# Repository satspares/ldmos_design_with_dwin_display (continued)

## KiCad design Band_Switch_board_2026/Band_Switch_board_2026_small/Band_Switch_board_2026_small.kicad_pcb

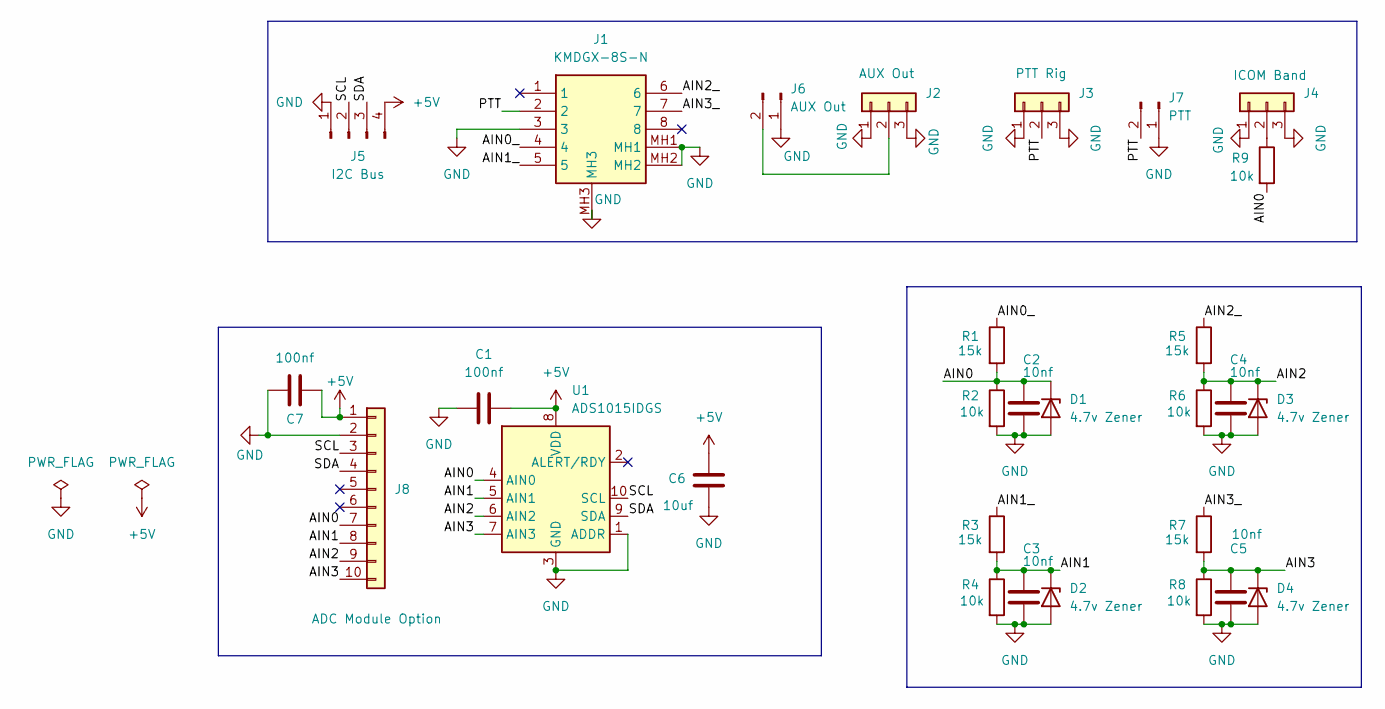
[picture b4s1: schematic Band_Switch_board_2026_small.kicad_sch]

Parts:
C1, C7: 100nf; C_Disc_D6.0mm_W2.5mm_P5.00mm
C2, C3, C4, C5: 10nf; C_Disc_D3.4mm_W2.1mm_P2.50mm
C6: 10uf; CP_Radial_Tantal_D5.0mm_P2.50mm
D1, D2, D3, D4: 4.7v Zener; D_DO-35_SOD27_P7.62mm_Horizontal
J1: KMDGX-8S-N; KMDGX8SN; Mouser Part Number 806-KMDGX-8S-N
J2: AUX Out; BarrelJack__Horizontal_Band_Switch
J3: PTT Rig; BarrelJack__Horizontal_Band_Switch
J4: ICOM Band; BarrelJack__Horizontal_Band_Switch
J5: I2C Bus; JST_EH_B4B-EH-A_1x04_P2.50mm_Vertical
J6: AUX Out; JST_EH_B2B-EH-A_1x02_P2.50mm_Vertical
J7: PTT; JST_EH_B2B-EH-A_1x02_P2.50mm_Vertical
J8: ADC Module Option; PinHeader_1x10_P2.54mm_Vertical_ADC
R1, R3, R5, R7: 15k; R_Axial_DIN0207_L6.3mm_D2.5mm_P7.62mm_Horizontal
R2, R4, R6, R8, R9: 10k; R_Axial_DIN0207_L6.3mm_D2.5mm_P7.62mm_Horizontal
U1: ADS1015IDGS; TSSOP-10_3x3mm_P0.5mm

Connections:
+5V: C1.2, C6.1, C7.2, J5.4, J8.1, U1.8 (VDD)
/AIN0: C2.1, D1.1 (K), J8.7, R1.2, R2.1, R9.2, U1.4 (AIN0)
/AIN0_: J1.4, R1.1
/AIN1: C3.1, D2.1 (K), J8.8, R3.2, R4.1, U1.5 (AIN1)
/AIN1_: J1.5, R3.1
/AIN2: C4.1, D3.1 (K), J8.9, R5.2, R6.1, U1.6 (AIN2)
/AIN2_: J1.6, R5.1
/AIN3: C5.1, D4.1 (K), J8.10, R7.2, R8.1, U1.7 (AIN3)
/AIN3_: J1.7, R7.1
/PTT: J1.2, J3.2, J7.2
/SCL: J5.2, J8.3, U1.10 (SCL)
/SDA: J5.3, J8.4, U1.9 (SDA)
GND: C1.1, C2.2, C3.2, C4.2, C5.2, C6.2, C7.1, D1.2 (A), D2.2 (A), D3.2 (A), D4.2 (A), J1.3, J1.MH1, J1.MH2, J1.MH3, J2.1, J2.3, J3.1, J3.3, J4.1, J4.3, J5.1, J6.1, J7.1, J8.2, R2.2, R4.2, R6.2, R8.2, U1.1 (ADDR), U1.3 (GND)
unnamed: J2.2, J6.2
unnamed: J4.2, R9.1

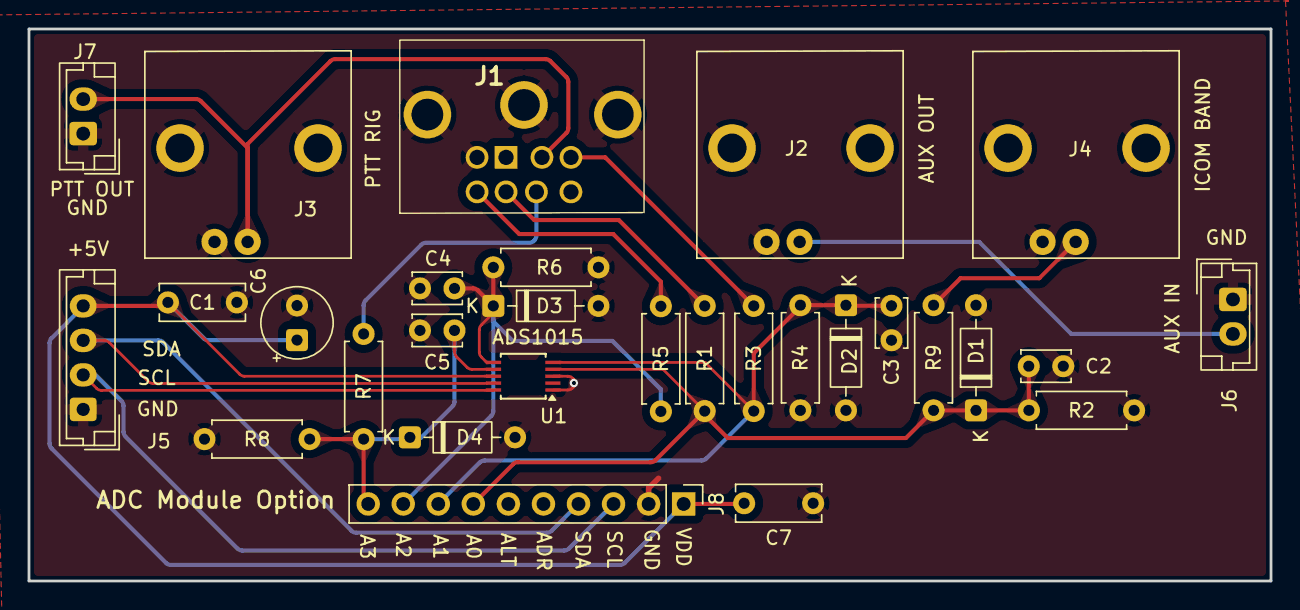
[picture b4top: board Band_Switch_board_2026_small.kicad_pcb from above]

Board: 2 copper layers, 90.0 x 40.0 mm, 29 parts (0 on the bottom side), 15 nets.

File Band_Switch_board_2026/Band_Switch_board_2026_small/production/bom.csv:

Designator,Footprint,Quantity,Value,LCSC Part #
"C1, C7",C_Disc_D6.0mm_W2.5mm_P5.00mm,2,100nf,
"C2, C3, C4, C5",C_Disc_D3.4mm_W2.1mm_P2.50mm,4,10nf,
C6,CP_Radial_Tantal_D5.0mm_P2.50mm,1,10uf,
"D1, D2, D3, D4",D_DO-35_SOD27_P7.62mm_Horizontal,4,4.7v Zener,
J1,KMDGX8SN,1,KMDGX-8S-N,
J2,BarrelJack__Horizontal_Band_Switch,1,AUX Out,
J3,BarrelJack__Horizontal_Band_Switch,1,PTT Rig,
J4,BarrelJack__Horizontal_Band_Switch,1,ICOM Band,
J5,JST_EH_B4B-EH-A_1x04_P2.50mm_Vertical,1,I2C Bus,
J6,JST_EH_B2B-EH-A_1x02_P2.50mm_Vertical,1,AUX Out,
J7,JST_EH_B2B-EH-A_1x02_P2.50mm_Vertical,1,PTT,
J8,PinHeader_1x10_P2.54mm_Vertical_ADC,1,ADC Module,
"R1, R3, R5, R7",R_Axial_DIN0207_L6.3mm_D2.5mm_P7.62mm_Horizontal,4,15k,
"R2, R4, R6, R8, R9",R_Axial_DIN0207_L6.3mm_D2.5mm_P7.62mm_Horizontal,5,10k,
U1,TSSOP-10_3x3mm_P0.5mm,1,ADS1015IDGS,

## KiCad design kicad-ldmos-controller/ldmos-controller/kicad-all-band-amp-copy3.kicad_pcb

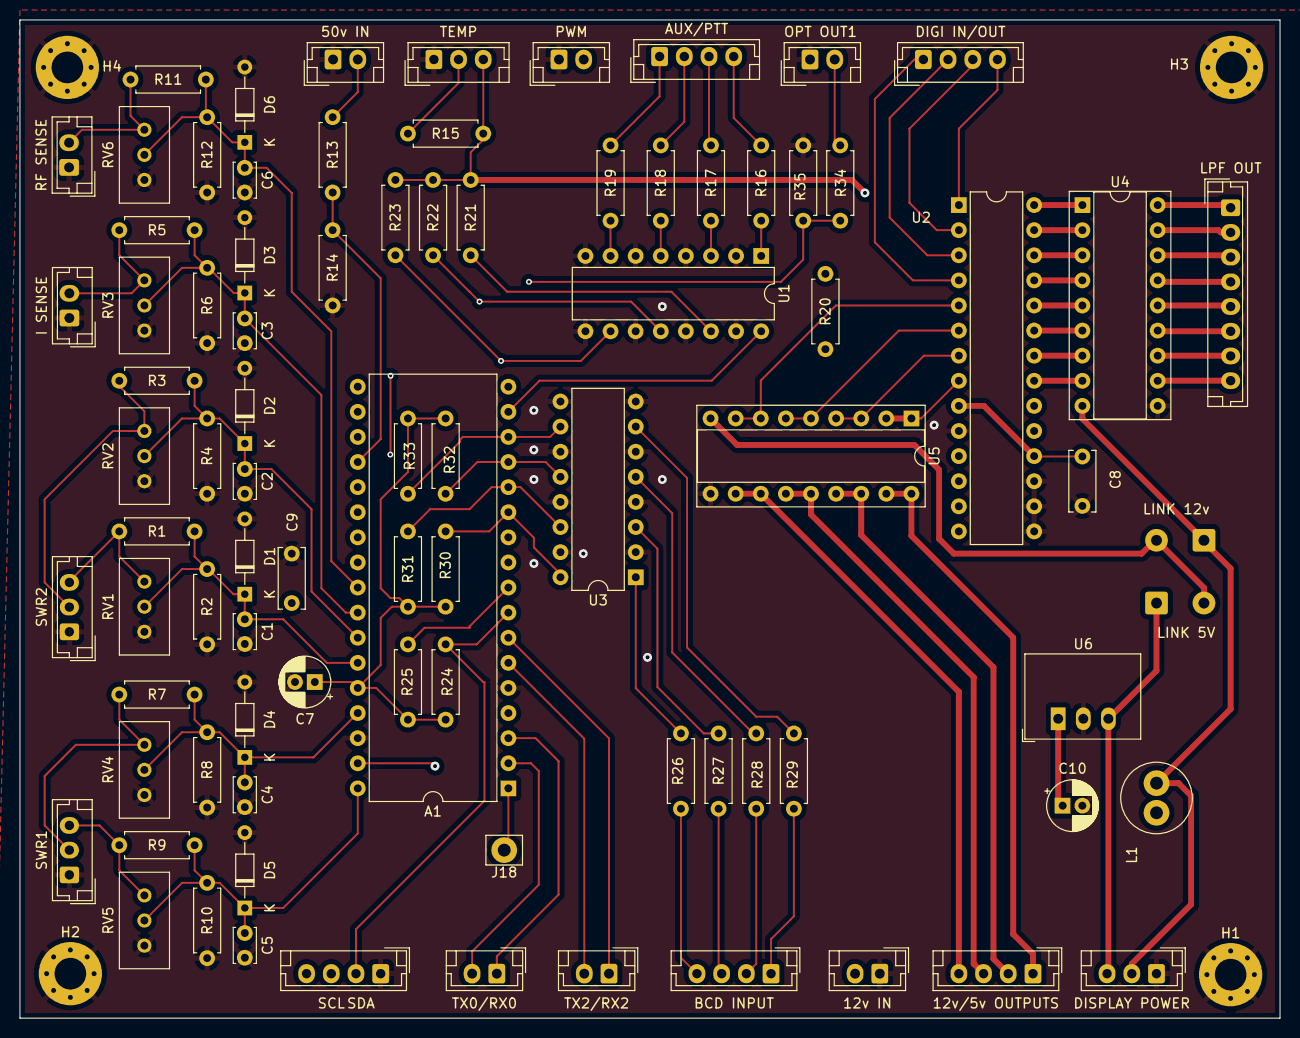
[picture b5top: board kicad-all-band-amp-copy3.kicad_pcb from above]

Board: 4 copper layers, 127.5 x 101.0 mm, 90 parts (0 on the bottom side), 84 nets.

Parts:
12v IN: 12v Input; JST_EH_B2B-EH-A_1x02_P2.50mm_Vertical
12v/5v OUTPUTS: 12v/5v Outputs; JST_EH_B4B-EH-A_1x04_P2.50mm_Vertical
50v IN: 50v In.; JST_EH_B2B-EH-A_1x02_P2.50mm_Vertical
A1: Arduino_Nano_Every-4808; DIP-34_W15.24mm
AUX/PTT: Ext. In; JST_EH_B4B-EH-A_1x04_P2.50mm_Vertical
BCD INPUT: BCD Input; JST_EH_B4B-EH-A_1x04_P2.50mm_Vertical
C1, C2, C3, C4, C5, C6: 1nf; C_Disc_D3.4mm_W2.1mm_P2.50mm
C7: 10uf; CP_Radial_D5.0mm_P2.00mm
C8, C9: 100nf; C_Disc_D6.0mm_W2.5mm_P5.00mm
C10: 2.2uf; CP_Radial_D5.0mm_P2.00mm
D1, D2, D3, D4, D5, D6: D_Zener; D_DO-34_SOD68_P7.62mm_Horizontal
DIGI IN/OUT: Digi In/Out; JST_EH_B4B-EH-A_1x04_P2.50mm_Vertical
DISPLAY POWER: DISPLAY POWER; JST_EH_B3B-EH-A_1x03_P2.50mm_Vertical
H1, H2, H3, H4: MountingHole_Pad; MountingHole_3.2mm_M3_Pad_Via
I SENSE: I detect; JST_EH_B2B-EH-A_1x02_P2.50mm_Vertical
J18: UPDI; Pin_D1.3mm_L10.0mm_W3.5mm_Flat
L1: L; L_Radial_D7.0mm_P3.00mm
LINK 5V, LINK 12v: Jumper_2_Open; SolderWire-0.5sqmm_1x02_P4.8mm_D0.9mm_OD2.3mm
LPF OUT: LPF; JST_EH_B8B-EH-A_1x08_P2.50mm_Vertical
OPT OUT1: 50v In.; JST_EH_B2B-EH-A_1x02_P2.50mm_Vertical
PWM: Conn_01x02_Pin; JST_EH_B2B-EH-A_1x02_P2.50mm_Vertical
R1, R2, R3, R4, R5, R6, R7, R8, R9, R10, R11, R12, R13, R14, R15, R16, R17, R18, R19, R20, R21, R22, R23, R24, R25, R26, R27, R28, R29, R30, R31, R32, R33, R34, R35: R; R_Axial_DIN0207_L6.3mm_D2.5mm_P7.62mm_Horizontal
RF SENSE: RF In Level; JST_EH_B2B-EH-A_1x02_P2.50mm_Vertical
RV1, RV2, RV3, RV4, RV5, RV6: R_Potentiometer; Potentiometer_Bourns_3296W_Vertical
SCL: I2c Output; JST_EH_B4B-EH-A_1x04_P2.50mm_Vertical
SWR1: SWR1; JST_EH_B3B-EH-A_1x03_P2.50mm_Vertical
SWR2: SWR2; JST_EH_B3B-EH-A_1x03_P2.50mm_Vertical
TEMP: Temp; JST_EH_B3B-EH-A_1x03_P2.50mm_Vertical
TX0/RX0: TX0/RX0; JST_EH_B2B-EH-A_1x02_P2.50mm_Vertical
TX2/RX2: TX2/RX2; JST_EH_B2B-EH-A_1x02_P2.50mm_Vertical
U1, U3: LTV-847; DIP-16_W7.62mm
U2: MCP23017_SP; DIP-28_W7.62mm
U4, U5: MIC2981/82YN; DIP-18_W7.62mm_Socket
U6: R-78E5.0-1.0; Converter_DCDC_RECOM_R-78E-0.5_THT

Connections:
+5F: DISPLAY POWER.3, LINK 5V.1 (A), U6.3 (OUT)
+5V: A1.22 (+5V), C7.1, C8.2, C9.1, R15.2, R20.2, R21.2, R22.2, R23.2, R24.1, R25.1, R30.2, R31.2, R32.2, R33.2, SCL.4, TEMP.3, U2.9 (VDD), U2.18 (~RESET)
/50V_IN: 50v IN.2, R13.1
/A2: A1.28 (D16/A2), R15.1, TEMP.2
/A4: A1.26 (D18/A4), C6.1, D6.1 (K), R11.2, R12.1, RV6.2
/A5: A1.25 (D19/A5), C3.1, D3.1 (K), R5.2, R6.1, RV3.2
/A6: A1.24 (D20/A6), C2.1, D2.1 (K), R3.2, R4.1, RV2.2
/A7: A1.23 (D21/A7), C1.1, D1.1 (K), R1.2, R2.1, RV1.2
/A11: A1.31 (D25/A11), R13.2, R14.1
/A24: A1.18 (24/A10), C5.1, D5.1 (K), R9.2, R10.1, RV5.2
/A26: A1.21 (A26), C4.1, D4.1 (K), R7.2, R8.1, RV4.2
/D6: A1.10 (D6), U2.19 (INTB)
/D8: A1.12 (D8), R30.1, U3.16
/D9: A1.13 (D9), R31.1, U3.14
/D10: A1.14 (D10), R32.1, U3.12
/D11: A1.15 (D11), R33.1, U3.10
/D12: A1.16 (SCK), R20.1, U1.16
/D13: A1.33 (D13), R34.2, R35.1
/D14: A1.30 (D14/A0), R22.1, U1.12
/D15: A1.29 (D15/A1), R23.1, U1.10
/D23: A1.34 (D23/A9), R21.1, U1.14
/FWD1: R9.1, RV5.1, SWR1.3
/FWD2: R1.1, RV1.1, SWR2.3
/PWM: A1.17 (D22/A8), PWM.2
/REV1: R7.1, RV4.1, SWR1.2
/REV2: R3.1, RV2.1, SWR2.2
/RF_LEVEL: R11.1, RF SENSE.2, RV6.1
/SCL: A1.9 (SCL_D5), R25.2, SCL.3, U2.12 (SCK)
/SDA: A1.8 (SDA_D4), R24.2, SCL.2, U2.13 (SDA)
/currrent: I SENSE.2, R5.1, RV3.1
GND: 12v IN.1, 50v IN.1, A1.5 (GND), A1.20 (GND), C1.2, C2.2, C3.2, C4.2, C5.2, C6.2, C7.2, C8.1, C9.2, C10.2, D1.2 (A), D2.2 (A), D3.2 (A), D4.2 (A), D5.2 (A), D6.2 (A), DISPLAY POWER.1, H1.1, H2.1, H3.1, H4.1, I SENSE.1, OPT OUT1.1, PWM.1, R2.2, R4.2, R6.2, R8.2, R10.2, R12.2, R14.2, R35.2, RF SENSE.1, RV1.3, RV2.3, RV3.3, RV4.3, RV5.3, RV6.3, SCL.1, SWR1.1, SWR2.1, TEMP.1, U1.2, U1.4, U1.6, U1.8, U1.9, U1.11, U1.13, U1.15, U2.10 (VSS), U2.15 (A0), U2.16 (A1), U2.17 (A2), U3.2, U3.4, U3.6, U3.8, U3.9, U3.11, U3.13, U3.15, U4.10 (GND), U5.10 (GND), U6.2 (GND)
unnamed: A1.3 (RXD0), TX0/RX0.1
unnamed: A1.7 (RXD2), TX2/RX2.1
unnamed: A1.2 (TXD0), TX0/RX0.2
unnamed: A1.6 (TXD2), TX2/RX2.2
unnamed: A1.1 (UDPI), J18.1
unnamed: AUX/PTT.1, R19.1
unnamed: AUX/PTT.2, R18.1
unnamed: AUX/PTT.3, R17.1
unnamed: AUX/PTT.4, R16.1
unnamed: BCD INPUT.1, R29.1
unnamed: BCD INPUT.2, R28.1
unnamed: BCD INPUT.3, R27.1
unnamed: BCD INPUT.4, R26.1
unnamed: LPF OUT.1, U4.18 (OUT1)
unnamed: LPF OUT.2, U4.17 (OUT2)
unnamed: LPF OUT.3, U4.16 (OUT3)
unnamed: LPF OUT.4, U4.15 (OUT4)
unnamed: LPF OUT.5, U4.14 (OUT5)
unnamed: LPF OUT.6, U4.13 (OUT6)
unnamed: LPF OUT.7, U4.12 (OUT7)
unnamed: LPF OUT.8, U4.11 (OUT8)
unnamed: DIGI IN/OUT.1, U2.4 (GPB3)
unnamed: DIGI IN/OUT.2, U2.3 (GPB2)
unnamed: DIGI IN/OUT.3, U2.2 (GPB1)
unnamed: DIGI IN/OUT.4, U2.1 (GPB0)
unnamed: 12v/5v OUTPUTS.1, U5.17 (OUT2), U5.18 (OUT1)
unnamed: 12v/5v OUTPUTS.2, U5.15 (OUT4), U5.16 (OUT3)
unnamed: 12v/5v OUTPUTS.3, U5.13 (OUT6), U5.14 (OUT5)
unnamed: 12v/5v OUTPUTS.4, U5.11 (OUT8), U5.12 (OUT7)
unnamed: OPT OUT1.2, R34.1
unnamed: R16.2, U1.1
unnamed: R17.2, U1.3
unnamed: R18.2, U1.5
unnamed: R19.2, U1.7
unnamed: R26.2, U3.1
unnamed: R27.2, U3.3
unnamed: R28.2, U3.5
unnamed: R29.2, U3.7
unnamed: U2.21 (GPA0), U4.8 (IN8)
unnamed: U2.22 (GPA1), U4.7 (IN7)
unnamed: U2.23 (GPA2), U4.6 (IN6)
unnamed: U2.24 (GPA3), U4.5 (IN5)
unnamed: U2.25 (GPA4), U4.4 (IN4)
unnamed: U2.26 (GPA5), U4.3 (IN3)
unnamed: U2.27 (GPA6), U4.2 (IN2)
unnamed: U2.28 (GPA7), U4.1 (IN1)
unnamed: U2.5 (GPB4), U5.7 (IN7), U5.8 (IN8)
unnamed: U2.6 (GPB5), U5.5 (IN5), U5.6 (IN6)
unnamed: U2.7 (GPB6), U5.3 (IN3), U5.4 (IN4)
unnamed: U2.8 (GPB7), U5.1 (IN1), U5.2 (IN2)
VCC: 12v IN.2, A1.19 (VIN), DISPLAY POWER.2, L1.2, LINK 12v.1 (A), U4.9 (VS)
VD: C10.1, L1.1, U6.1 (IN)
VPP: LINK 5V.2 (B), LINK 12v.2 (B), U5.9 (VS)

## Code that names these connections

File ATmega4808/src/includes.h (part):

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const uint16_t MainText2_Color = COLOR_WHITE;

/* ======= SWR Progress Bar Max Display eg. 200=2.00 swr 300=3.00 swr or other swr value * 100 ======== */
const uint16_t swrRangeMax = 250;  // 250 swr graph max is swr 2.50
const uint16_t powerRangeMax = 800; // Max Power graph range eg. 600=600 watts

/* ======= TX delay before tx needed for slow relays ======== */
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const uint8_t band_display_offset = 0;   // display first band icons 80m-4m
#endif

uint8_t swrOffset = 0;          // offset into eeprom for swr/lpf

bool temp_id_reset = false;     // ticker reset for temp and ID
bool peak_hold_reset = false;   // ticker reset for power peak hold etc
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// ************** Page 1 power calc page ***********
// Display controls
const uint16_t startPage_band_text = 0x5030;        //String 21 dec
const uint16_t startPage_swr_text = 0x5060;         //String 21 dec also used on page 4 swr calc
const uint16_t power_display_startPage = 0x2402;    // power in watt display
const uint16_t display_power_set_point = 0x2404;// power set point

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const uint8_t band4Mtr_switch =     0b00000001;

// MCP23017 port B pins 
const uint8_t A600BIAS = 8;   //< pin GPB0 (1) of the MCP23017. via. resistor split
const uint8_t GBP1 = 9;   //< pin GPB1 (2) of the MCP23017. Transistor Base
const uint8_t DX_RESET = 10;  //< pin GPB2 (3) of the MCP23017.
const uint8_t RELAY2 = 11;  //< pin GPB3 (4) of the MCP23017.
const uint8_t GPB4 = 12;  //< pin GPB4 (5) of the MCP23017.
const uint8_t GPB5 = 13;  //< pin GPB5 (6) of the MCP23017.
const uint8_t ANTSWITCH = 14;  //< pin GPB6 (7) of the MCP23017.
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#define REF2 A6
#define ID_IN A5
#define RFSENSE A4
#define PTT 12
#define LED_I 23
#define LED_PO 14
#define LED_SWR 15
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
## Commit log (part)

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2025-03-28 add kicad design
2025-03-28 add source files
2025-03-29 Add Display Files and documents
2025-03-29 force eeprom read after power and swr calc
2025-03-29 add image add dwin tool
2025-03-29 add pdf file
2025-03-29 add images
2025-03-29 add current unused functions
2025-03-31 bug fixes
2025-03-31 move icons
2025-04-01 update images and kernels
2025-04-01 update to v1.3.5 fix stuck display
2025-04-02 update icons change 1 kicad component
2025-04-02 add reset fuction update to v1.3.6
2025-04-03 upload image
2025-04-05 Fix antenna recall on boot change dsb1820 timeout
2025-04-06 Fit temperature beep at boot
2025-04-10 Improve SWR adjustment Add library and test functions for ADS1115
2025-04-11 Add max swr display range option
2025-04-11 Update includes.h
    Change variable type
2025-04-12 Make power bar max setting easier
2025-04-12 Fix incorrect swr millivolt display
2025-04-13 remove 8031 files
2025-06-04 Add missing control
2025-06-05 Fix missing odrive error indicator
2025-06-05 add attenuator pcb
2025-10-07 Add save drive settings per. band
2025-10-11 Update platformio.ini
    Change CPU speed to board default
2026-01-25 Add info files
2026-04-28 new software
2026-04-28 add folder
2026-04-28 new files
2026-04-28 rename files
2026-04-30 change componet values
2026-04-30 update functions
2026-05-01 improve display
2026-05-02 change eeeprom settings
2026-05-03 add icom auto band switch NOT tested
2026-05-03 update dwin functions
2026-05-03 update pcb boards
2026-05-04 update pcb files to kicad 10
2026-05-04 update pcb
2026-05-04 update n-con-board
2026-05-04 remove backup files
2026-05-05 update pcb's
2026-05-05 improve code
2026-05-06 update component values
2026-05-06 tidy code
2026-05-06 remove debug print
2026-06-05 small uodate
2026-06-07 change some values - alter boards
2026-06-23 add swr trip output
